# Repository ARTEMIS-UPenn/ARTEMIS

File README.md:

ARTEMIS
=======

Code associated with the ARTEMIS project

Prepare your computer
=====================
sudo apt-get install openssh-server openssh-client git
ssh-keygen -t rsa
add public rsa key to ARTEMIS git repo
git clone git@github.com:ARTEMIS-UPenn/ARTEMIS.git

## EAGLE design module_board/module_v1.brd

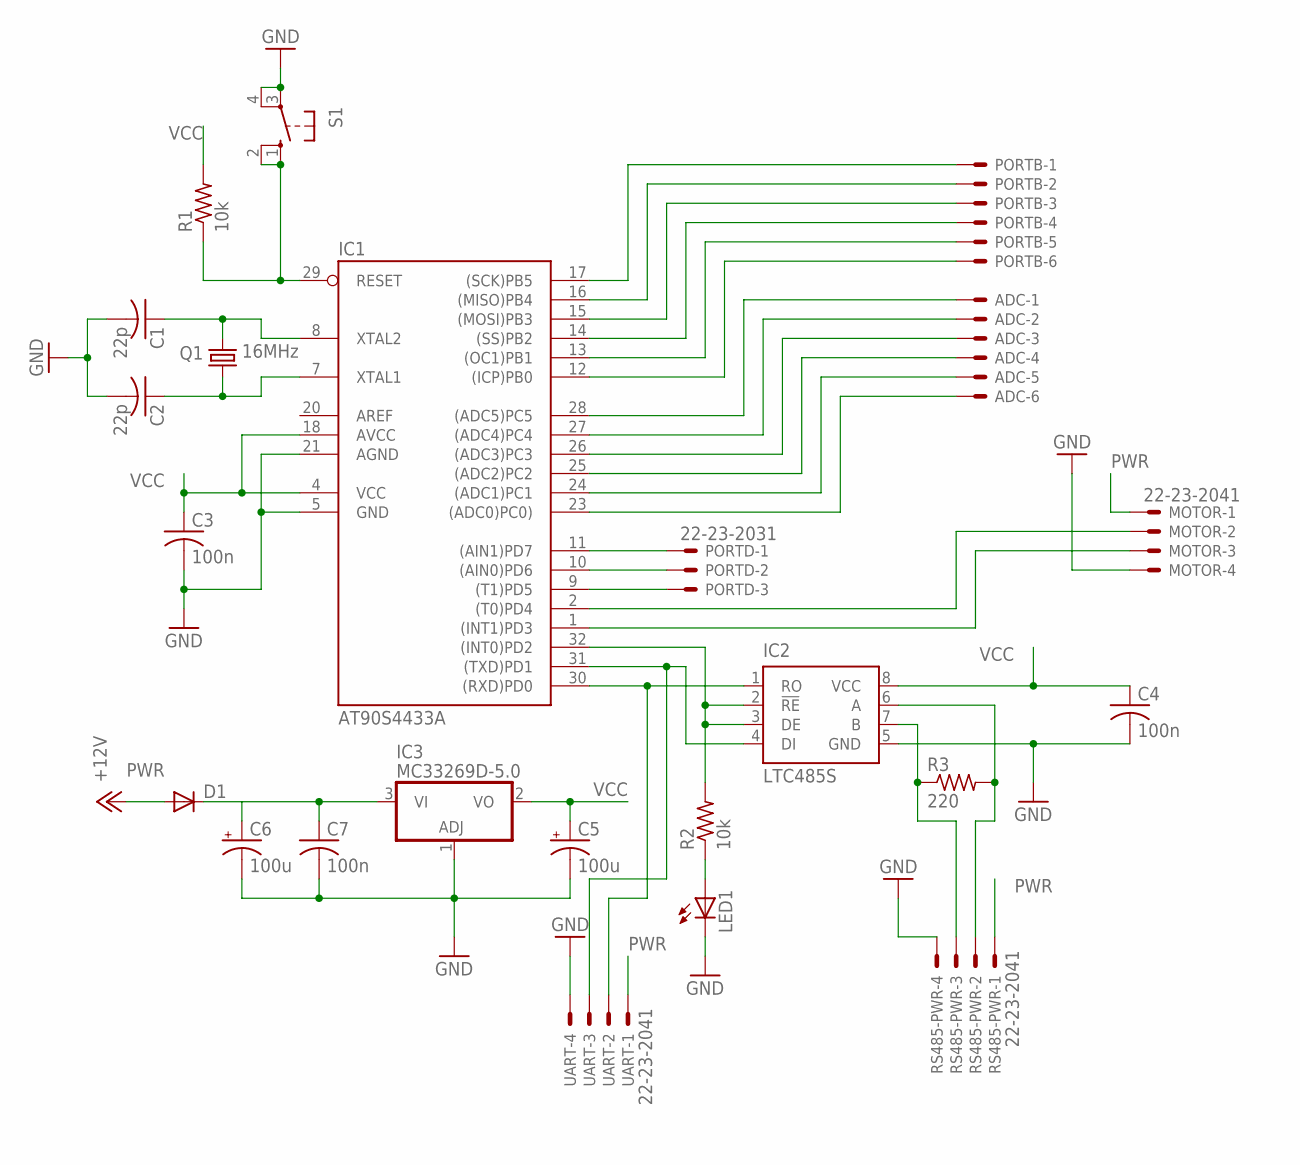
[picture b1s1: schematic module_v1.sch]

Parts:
ADC: 22-23-2061
C1, C2: 22p; C0805
C3, C4, C7: 100n; C0805
C5, C6: 100u; PANASONIC_D
D1: DIODE-SMB; SMB
IC1: AT90S4433A; TQFP32-08
IC2: LTC485S; SOIC8
IC3: MC33269D-5.0; DPACK
LED1: LEDCHIP-LED0805; CHIP-LED0805
MOTOR: 22-23-2041
PORTB: 22-23-2061
PORTD: 22-23-2031
Q1: 16MHz; HC49/S
R1, R2: 10k; R0805
R3: 220; R0805
RS485-PWR: 22-23-2041
S1: 10-XX; B3F-10XX
UART: 22-23-2041

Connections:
GND: C1.2, C2.2, C3.2, C4.2, C5.-, C6.-, C7.2, IC1.5 (GND), IC1.21 (AGND), IC2.5 (GND), IC3.1 (ADJ), LED1.C, MOTOR.4, RS485-PWR.4, S1.3, S1.4 (P1), UART.4
unnamed: IC1.29 (RESET), R1.1, S1.1 (S), S1.2 (S1)
unnamed: C2.1, IC1.7 (XTAL1), Q1.1
unnamed: IC1.32 ((INT0)PD2), IC2.2 (!RE), IC2.3 (DE), R2.2
unnamed: C1.1, IC1.8 (XTAL2), Q1.2
unnamed: IC1.30 ((RXD)PD0), IC2.1 (RO), UART.2
unnamed: IC1.31 ((TXD)PD1), IC2.4 (DI), UART.3
unnamed: IC2.7 (B), R3.1, RS485-PWR.3
unnamed: IC2.6 (A), R3.2, RS485-PWR.2
unnamed: LED1.A, R2.1
unnamed: IC1.1 ((INT1)PD3), MOTOR.3
unnamed: IC1.2 ((T0)PD4), MOTOR.2
unnamed: ADC.6, IC1.23 ((ADC0)PC0))
unnamed: ADC.5, IC1.24 ((ADC1)PC1)
unnamed: ADC.4, IC1.25 ((ADC2)PC2)
unnamed: ADC.3, IC1.26 ((ADC3)PC3)
unnamed: ADC.2, IC1.27 ((ADC4)PC4)
unnamed: ADC.1, IC1.28 ((ADC5)PC5)
unnamed: IC1.12 ((ICP)PB0), PORTB.6
unnamed: IC1.13 ((OC1)PB1), PORTB.5
unnamed: IC1.14 ((SS)PB2), PORTB.4
unnamed: IC1.15 ((MOSI)PB3), PORTB.3
unnamed: IC1.16 ((MISO)PB4), PORTB.2
unnamed: IC1.17 ((SCK)PB5), PORTB.1
unnamed: C6.+, C7.1, D1.C, IC3.3 (VI)
unnamed: IC1.9 ((T1)PD5), PORTD.3
unnamed: IC1.10 ((AIN0)PD6), PORTD.2
unnamed: IC1.11 ((AIN1)PD7), PORTD.1
PWR: D1.A, MOTOR.1, RS485-PWR.1, UART.1
VCC: C3.1, C4.1, C5.+, IC1.4 (VCC), IC1.18 (AVCC), IC2.8 (VCC), IC3.2 (VO), R1.2

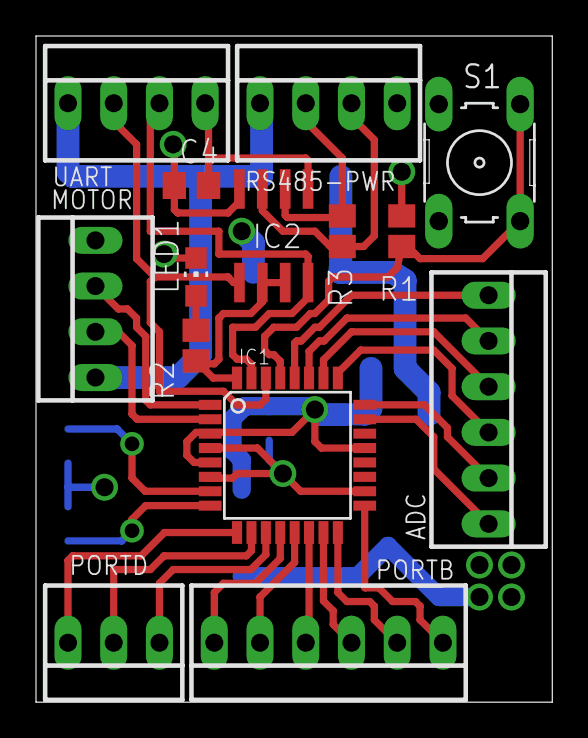
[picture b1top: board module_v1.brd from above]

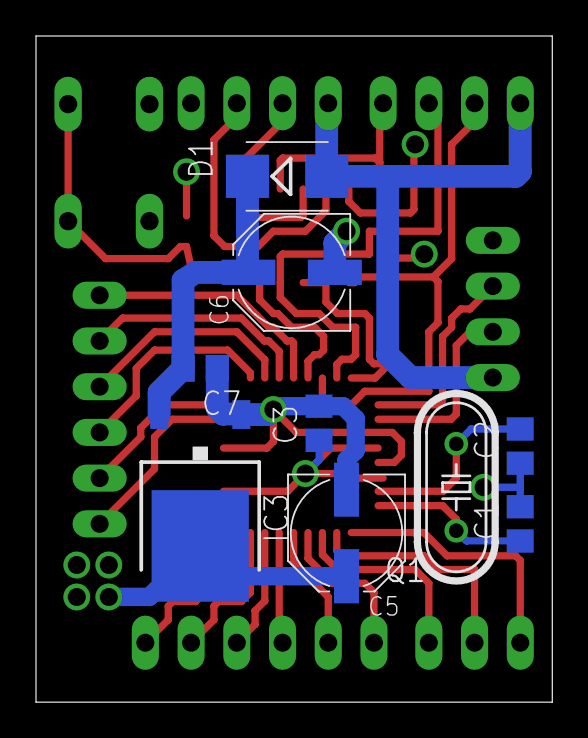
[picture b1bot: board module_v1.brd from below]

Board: 4 copper layers, 28.7 x 37.0 mm, 23 parts (9 on the bottom side), 30 nets.

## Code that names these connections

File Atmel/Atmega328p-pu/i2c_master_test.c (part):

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      switch ( pressedButton ) 
      {
        // Send a Generall Call
        case (1<<PD0):      
          messageBuf[0] = TWI_GEN_CALL;     // The first byte must always consit of General Call code or the TWI slave address.
          messageBuf[1] = 0xAA;             // The command or data to be included in the general call.
          TWI_Start_Transceiver_With_Data( messageBuf, 2 );
          break;

        // Send a Address Call, sending a command and data to the Slave          
        case (1<<PD1):      
          messageBuf[0] = (TWI_targetSlaveAddress<<TWI_ADR_BITS) | (FALSE<<TWI_READ_BIT); // The first byte must always consit of General Call code or the TWI slave address.
          messageBuf[1] = TWI_CMD_MASTER_WRITE;             // The first byte is used for commands.
          messageBuf[2] = myCounter;                        // The second byte is used for the data.
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          break;

        // Send a Address Call, sending a request, followed by a resceive          
        case (1<<PD2):      
          // Send the request-for-data command to the Slave
          messageBuf[0] = (TWI_targetSlaveAddress<<TWI_ADR_BITS) | (FALSE<<TWI_READ_BIT); // The first byte must always consit of General Call code or the TWI slave address.
          messageBuf[1] = TWI_CMD_MASTER_READ;             // The first byte is used for commands.
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                                                // section further down in the code.
                    
        // Get status from Transceiver and put it on PORTB
        case (1<<PD5):
          PORTB = TWI_Get_State_Info();
          break;

        // Increment myCounter and put it on PORTB          
        case (1<<PD6):      
          PORTB = ++myCounter;        
          break;
          
        // Reset myCounter and put it on PORTB
        case (1<<PD7):      
          PORTB = myCounter = 0;        
          break;  
      }
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
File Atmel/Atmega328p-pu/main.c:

// standard c library
#include <stdio.h>
#include <string.h>
#include <stdbool.h>
#include <stdint.h>
#include <math.h>
#include <util/delay.h>

// avr library
#include <avr/io.h>
#include <avr/interrupt.h>
#include <avr/eeprom.h>

// common libraries
#include "uart.h"
#include "DataPacket.h"


#define MOTOR_EN PD3
#define MOTOR_P1 PD4
#define MOTOR_P2 PD5
#define IND_LED PD6

// packet instruction types
enum {
  READ_CMD = 0x01,
  WRITE_CMD
};

// write instructions
enum {
  DISPENSE = 0x01,
  RETRACT,
  UNLOCK,
  CHANGE_ID,
  LED
};

// read instructions
enum {
  STATUS = 0x01,
  ITEM_COUNT
};
  
// compartment status
enum {
  INITIALIZING = 0x00,
  STANDBY = 0x01,
  DISPENSING = 0x02,
  RETRACTING = 0x04,
  DRAWER_OPEN = 0x08,
  DRAWER_CLOSED = 0x10,
  JAM = 0x20,
  DOOR_OPEN = 0x40
};

volatile uint8_t SYS_STATE = INITIALIZING;
uint8_t MMC_ID;

// when tray is fully opened, limit switch is pressed
ISR(PCINT0_vect) {
  if (SYS_STATE == RETRACTING) {
    PORTD |= (1 << MOTOR_P1) | (1 << MOTOR_P2);
    SYS_STATE = STANDBY | DRAWER_CLOSED;
  }  
}

ISR(PCINT1_vect) {
  if (SYS_STATE == DISPENSING) {
    PORTD |= (1 << MOTOR_P1) | (1 << MOTOR_P2);
    SYS_STATE = STANDBY | DRAWER_OPEN;
  }
}

// hardware initialization
void init() {
  cli();                      // clear global interrupts
  
  PCICR |= (1 << 1) | (1 << 0); // use pin change interrupt alternate function
  PCMSK1 |= (1 << 0); // enable pin change interrupt 8-14
  PCMSK0 |= (1 << 0);
  
  MMC_ID = eeprom_read_byte((uint8_t*)46); // set device id
  if (MMC_ID == 0xFF)
    MMC_ID = 0xFE;
  DDRB = 0xFC;
  PORTB = 0x00;
  DDRD |= (1 << MOTOR_EN) | (1 << MOTOR_P1) | (1 << MOTOR_P2) | (1 << IND_LED); // set motor pins
  PORTD |= (1 << MOTOR_EN) | (1 << MOTOR_P1) | (1 << MOTOR_P2); // set motor to idle
  uart0_init();
  uart0_setbaud(57600);
  sei();
  SYS_STATE = STANDBY | DRAWER_CLOSED;
}

int main(void) {
  init();
  
  Packet host_packet;
  PacketInit(&host_packet);
  int len = 0;
  char c;
  while(1) {
    c = uart0_getchar();
    if (c != EOF) {
      len = PacketProcessChar(&host_packet, c);
    }
    if (len > 0) {
      if (PacketGetId(&host_packet) == MMC_ID) { // id position
	switch (PacketGetType(&host_packet)) { // instr position
	case READ_CMD:
	  {
	    int pl_size = PacketGetPayloadSize(&host_packet);
	    uint8_t *pl = PacketGetData(&host_packet);
	    int i = 0;
	    if (pl_size > 0) {
	      switch(pl[i++]) {
	      case STATUS:
		{
		  uint8_t outbuf[6] = {0xFF, 0xFF, MMC_ID, 0x02, SYS_STATE, 0x00};
		  outbuf[5] = ~(MMC_ID + 0x02 + SYS_STATE);
		  int i;
		  for (i = 0; i < 6; i++)
		    uart0_putchar(outbuf[i]);
		  break;
		}
	      default:
		break;
	      }
	    }
	    break;
	  }
	case WRITE_CMD:
	  {
	    int pl_size = PacketGetPayloadSize(&host_packet);
	    uint8_t *pl = PacketGetData(&host_packet);
	    int i = 0;
	    if (pl_size > 0) {
	      switch(pl[i++]) { // payload 0 position
	      case DISPENSE:
		if (SYS_STATE == STANDBY | DRAWER_CLOSED) {
		  SYS_STATE = DISPENSING;
		  PORTD |= (1 << MOTOR_P2);
		  PORTD &= ~(1 << MOTOR_P1);
		}
		break;
	      case RETRACT:
		if (SYS_STATE == STANDBY | DRAWER_OPEN) {
		  SYS_STATE = RETRACTING;
		  PORTD |= (1 << MOTOR_P1);
		  PORTD &= ~(1 << MOTOR_P2);
		}
		break;
	      case UNLOCK:
		//TODO
		break;
	      case CHANGE_ID:
		if (i <= pl_size) {
		  eeprom_update_byte((uint8_t*)46, pl[i]);
		  MMC_ID = eeprom_read_byte((uint8_t*)46);
		}
		break;
	      case LED:
		if (i <= pl_size) {
		  switch (pl[i++]) { // payload 1 position
		  case 0x00: // turn off LED
		    PORTD &= ~(1 << IND_LED);
		    break;
		  case 0x01: // turn on LED
		    PORTD |= (1 << IND_LED);
		    break;
		  case 0x02: // toggle LED
		    PORTD ^= (1 << IND_LED);
		    break;
		  default:
		    break;
		  } // payload 1 position
		}
		break;
	      default:
		break;
	      } // payload 0 position
	    }
	    break;
	  }
	default:
	  break;
	} // instr position
      } // id position
      len = 0;
      }
  }
  return 0;
}

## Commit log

2013-11-07 first ARTEMIS commit
2013-11-07 first local commit
2013-11-07 test commit
2013-11-07 reset to head
2013-11-07 https root directory added
2013-11-08 starter app added
2013-11-09 added entry page and two buttons to redirect to catalog page. also added some styling and background image to main page banner
2013-11-09 some styling for main page title
2013-11-10 finished main page layout and started with inventory and toolcheckout pages
2013-11-16 more styling stuff
2013-11-16 added reporting system, need to implement file access and read/write
2013-11-19 test reporting gui
2013-11-19 demo ready
2014-01-21 added circular buffer code for UART com
2014-01-21 added code comments to CircBuf.h
2014-01-21 added sample micro code
2014-01-22 Makefile stuff for flashing
2014-01-22 UART com finished
2014-01-27 added gtk startup and some changes to micro code, plus manifest for chrome app
2014-01-30 gtk gui helloworld
2014-01-31 python gui test with kivy example
2014-02-04 communication protocol done
2014-02-05 servo testing code done
2014-02-05 removed unnecessary files
2014-02-12 reorganization for different micros
2014-02-12 i2c library for atmel chips with TWI module
2014-02-12 i2c test code
2014-02-12 renamed ARTEMIS_micro directory
2014-02-13 Atmega328p uart and led light up test done
2014-02-13 clean up and TWI slave code
2014-02-25 master code with rs485
2014-02-25 slave code with rs485
2014-02-25 modifications for overcoming 0xFF vs EOF boundary
2014-02-25 removed TWI I2C stuff
2014-02-25 removed slave i2c twi stuff
2014-02-25 removed twi include in main
2014-02-25 removed twi include in master code
2014-02-25 modified master rs485 code
2014-03-14 last commit before wiping Ubuntu on computer
2014-03-14 design for custom board
2014-03-14 script to install all dev packages
2014-03-14 edited README for initial instal script for development
2014-03-15 Added ARTEMIS app stuff and test python code
2014-03-15 no changes, just consistency
2014-03-15 all necessary packages updated
2014-03-16 finished sample serial code. rs485 and protocol work
2014-03-16 led toggling finished
2014-03-16 eeprom id done
2014-03-16 some changes to demo eeprom read/write
2014-03-18 added LAMP stack install and kivy install
2014-03-29 catching up. added withdraw code and close code plus serial python and datapacket library
2014-03-31 electronics work, status message, dispensing and retracting, led, id change and eeprom
2014-04-15 tried with 3rd limit switch, didn't work. new approach in next commit
2014-04-15 different pin assignments to use both ext interrupts and pcint, RST pin changed in uart.c
2014-04-15 everything is fixed. tray detection now works. working copy is in Atmega328_v2
2014-04-18 loop for durability test
